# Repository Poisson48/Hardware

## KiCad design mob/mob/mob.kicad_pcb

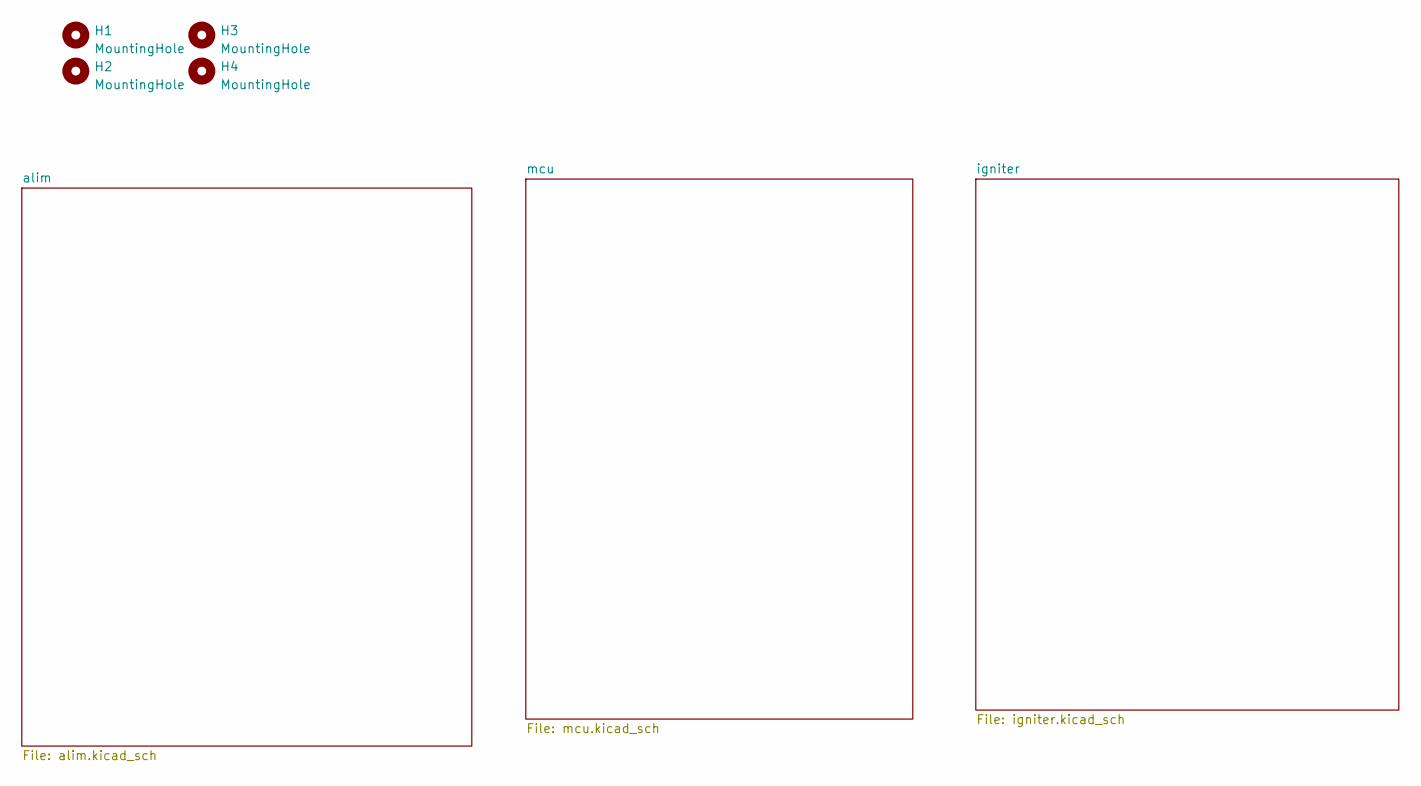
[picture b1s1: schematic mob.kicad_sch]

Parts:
H1, H2, H3, H4: MountingHole; MountingHole_3.2mm_M3_DIN965_Pad

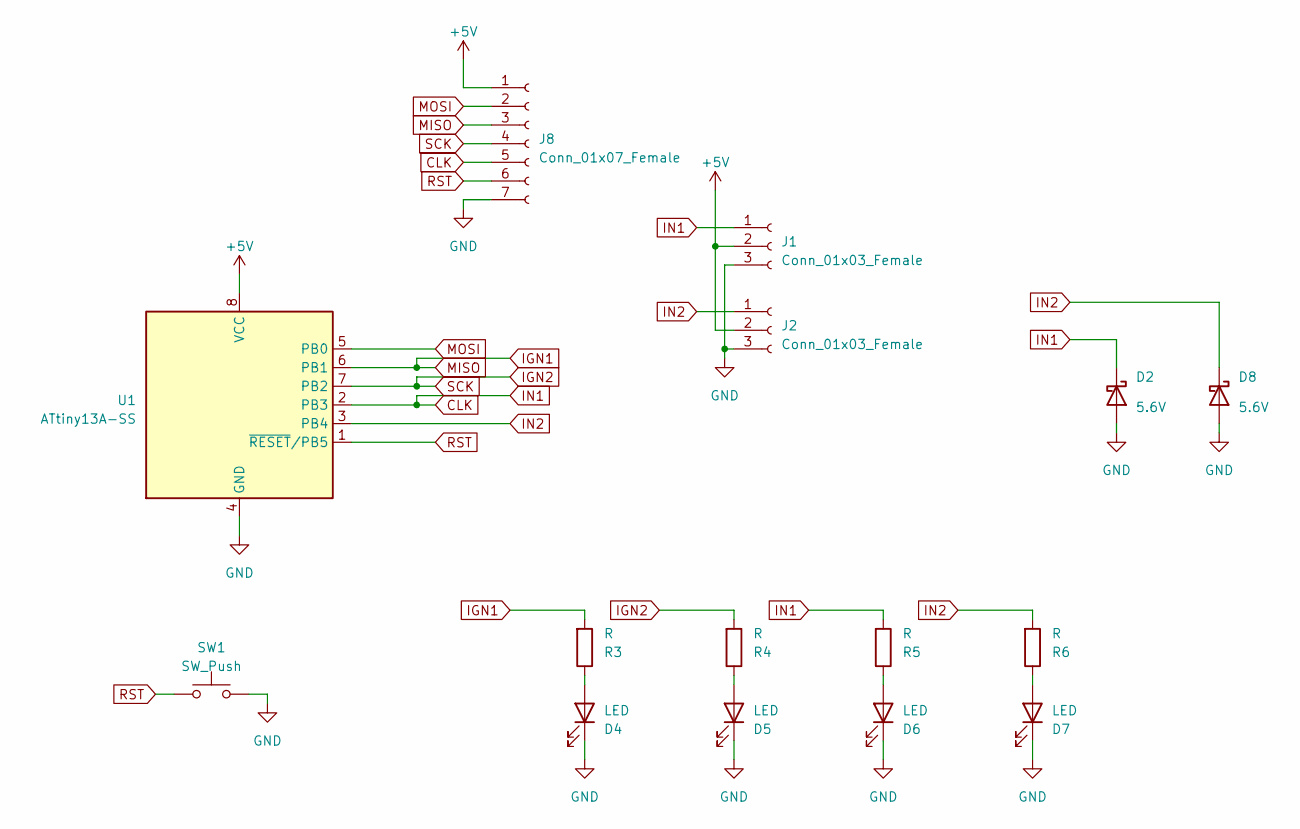
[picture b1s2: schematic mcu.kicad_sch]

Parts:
D2, D8: 5.6V; D_SOD-123
D4, D5, D6, D7: LED; D_0805_2012Metric
J1, J2: Conn_01x03_Female; PinSocket_1x03_P2.54mm_Vertical
J8: Conn_01x07_Female; PinSocket_1x07_P2.54mm_Vertical
R3, R4, R5, R6: R; R_0805_2012Metric
SW1: SW_Push; SW_PUSH_6mm
U1: ATtiny13A-SS; SOIC-8_3.9x4.9mm_P1.27mm

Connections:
+5V: J1.2, J2.2, J8.1, U1.8 (VCC); also elsewhere on the board
CLK: D2.1 (K), J1.1, J8.5, R5.2, U1.2 (PB3)
GND: D2.2 (A), D4.1 (K), D5.1 (K), D6.1 (K), D7.1 (K), D8.2 (A), J1.3, J2.3, J8.7, SW1.2, U1.4 (GND); also elsewhere on the board
IGN1: J8.3, R3.2, U1.6 (PB1); also elsewhere on the board
IGN2: J8.4, R4.2, U1.7 (PB2); also elsewhere on the board
IN2: D8.1 (K), J2.1, R6.2, U1.3 (PB4)
MOSI: J8.2, U1.5 (PB0)
unnamed: D4.2 (A), R3.1
unnamed: D5.2 (A), R4.1
unnamed: D6.2 (A), R5.1
unnamed: D7.2 (A), R6.1
RST: J8.6, SW1.1, U1.1 (~RESET/PB5)

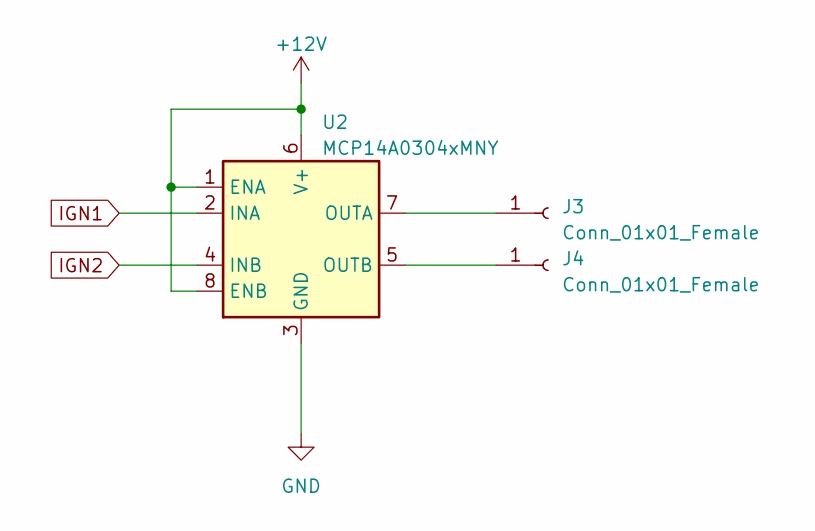
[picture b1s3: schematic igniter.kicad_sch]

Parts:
J3, J4: Conn_01x01_Female; Pin_D1.3mm_L11.0mm_LooseFit
U2: MCP14A0304xMNY; WDFN-8-1EP_3x2mm_P0.5mm_EP1.3x1.4mm

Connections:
+12V: U2.1 (ENA), U2.6 (V+), U2.8 (ENB); also elsewhere on the board
GND: U2.3 (GND), U2.9 (GND); also elsewhere on the board
IGN1: U2.2 (INA); also elsewhere on the board
IGN2: U2.4 (INB); also elsewhere on the board
unnamed: J3.1, U2.7 (OUTA)
unnamed: J4.1, U2.5 (OUTB)

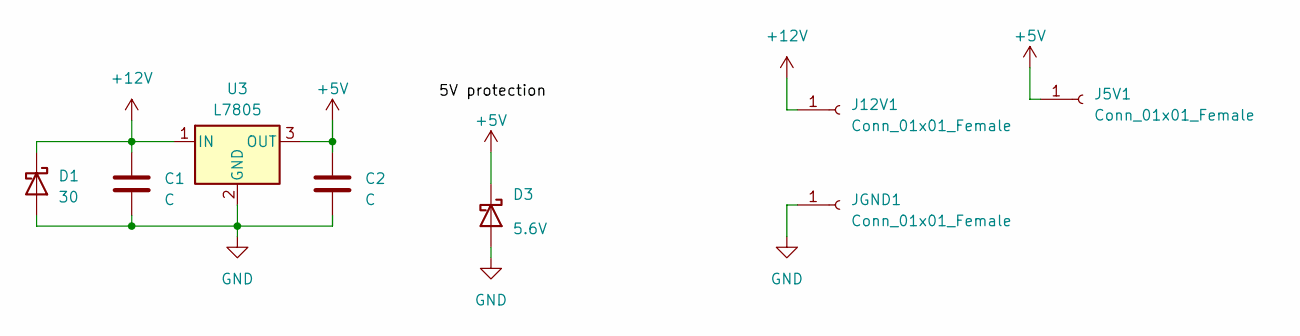
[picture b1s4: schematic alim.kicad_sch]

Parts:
C1, C2: C; C_1206_3216Metric
D1: 30; D_SOD-123
D3: 5.6V; D_SOD-123
J5V1, J12V1: Conn_01x01_Female; Pin_D1.3mm_L11.0mm_LooseFit
JGND1: Conn_01x01_Female; Pin_D1.3mm_L11.0mm_LooseFit
U3: L7805; TO-252-2

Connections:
+5V: C2.2, D3.1 (K), J5V1.1, U3.3 (OUT); also elsewhere on the board
+12V: C1.2, D1.1 (K), J12V1.1, U3.1 (IN); also elsewhere on the board
GND: C1.1, C2.1, D1.2 (A), D3.2 (A), JGND1.1, U3.2 (GND); also elsewhere on the board

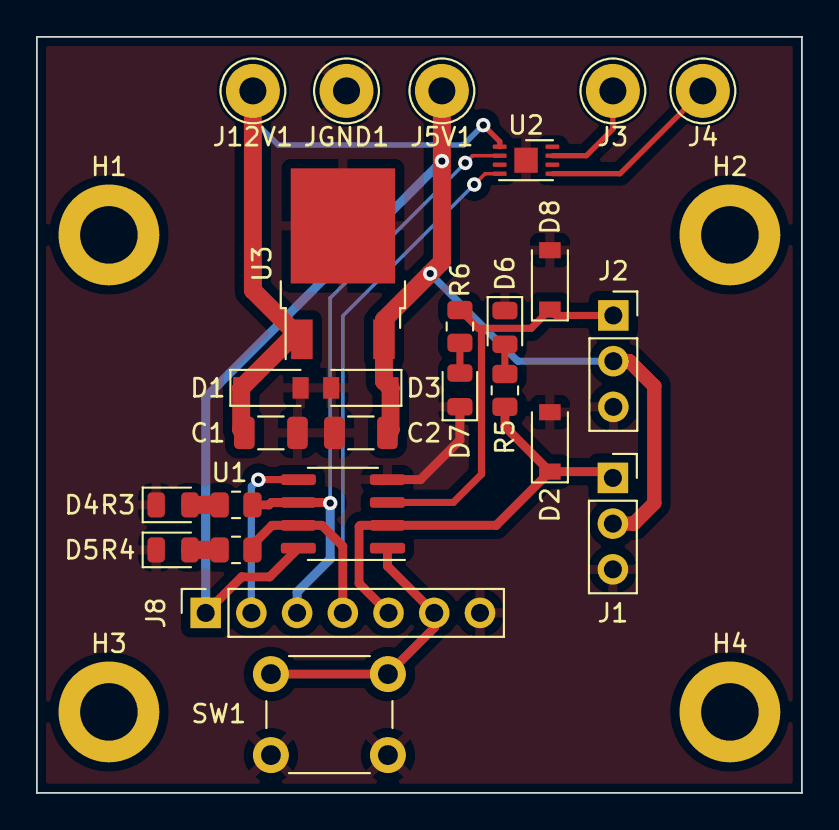
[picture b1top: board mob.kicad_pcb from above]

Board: 2 copper layers, 42.5 x 42.0 mm, 30 parts (0 on the bottom side), 15 nets.

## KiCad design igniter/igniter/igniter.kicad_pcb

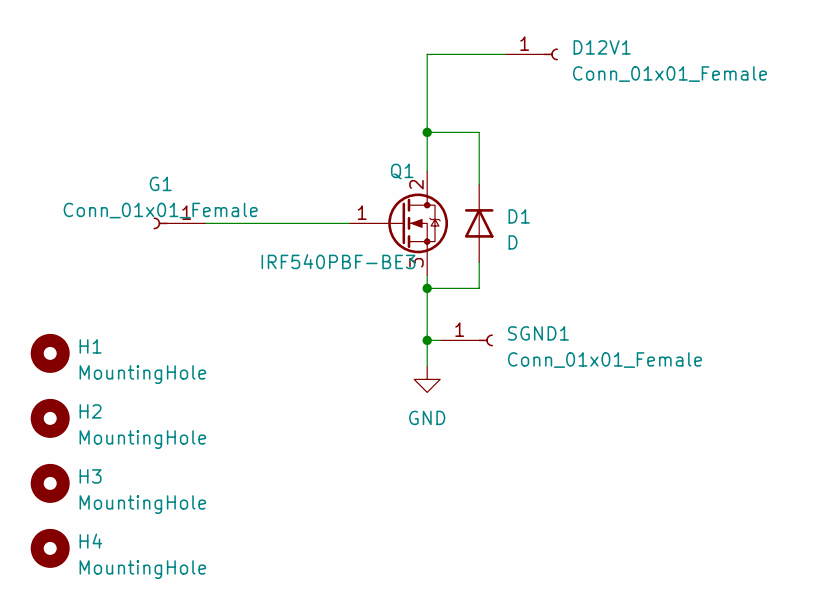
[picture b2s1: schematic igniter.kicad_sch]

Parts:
D1: D; TO-220-2_Horizontal_TabDown
D12V1: Conn_01x01_Female; Pin_D1.3mm_L11.0mm_LooseFit
G1: Conn_01x01_Female; Pin_D1.3mm_L11.0mm_LooseFit
H1, H2, H3, H4: MountingHole; MountingHole_3.2mm_M3_DIN965_Pad
Q1: IRF540PBF-BE3; TO-220-3_Horizontal_TabDown
SGND1: Conn_01x01_Female; Pin_D1.3mm_L11.0mm_LooseFit

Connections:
GND: D1.2 (A), Q1.3 (S), SGND1.1
unnamed: D1.1 (K), D12V1.1, Q1.2 (D)
unnamed: G1.1, Q1.1 (G)

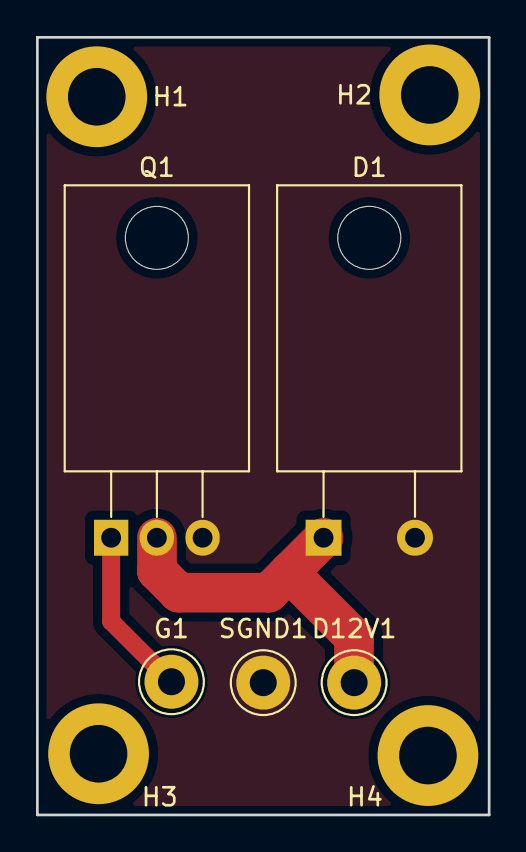
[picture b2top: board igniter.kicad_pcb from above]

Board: 2 copper layers, 25.1 x 43.2 mm, 9 parts (0 on the bottom side), 3 nets.

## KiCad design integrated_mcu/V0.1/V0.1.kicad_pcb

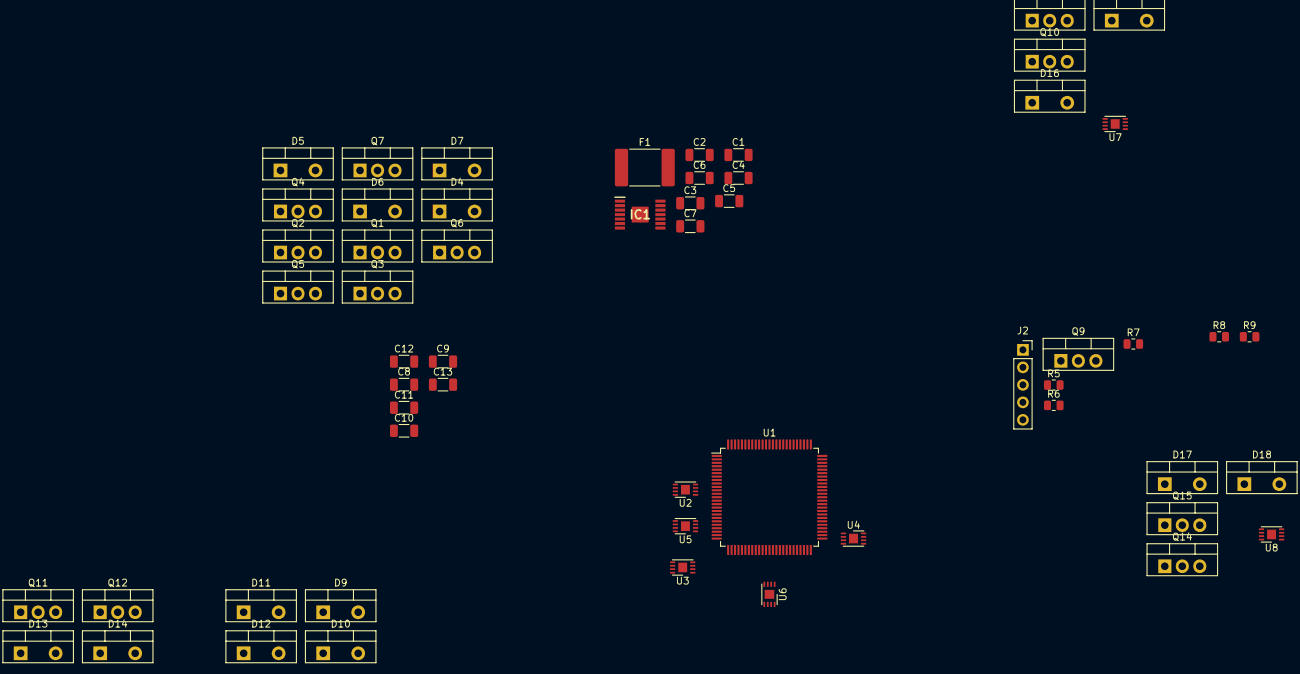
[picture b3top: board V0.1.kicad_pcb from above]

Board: 2 copper layers, 57 parts (0 on the bottom side), 59 nets, no tracks yet.

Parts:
C1, C4, C6, C7, C9, C10, C11, C12, C13: C; C_1206_3216Metric
C2, C3: 1μF; C_1206_3216Metric
C5: 10μF; C_1206_3216Metric
C8: 100nF; C_1206_3216Metric
D4, D5, D6, D7, D9, D10, D11, D12, D13, D14, D15, D16, D17, D18: D; TO-220-2_Vertical
F1: 576-2920L700/24SLER; Fuse_2920_7451Metric
IC1: TPS54225TPWPRQ1; SOP65P640X120-15N
J2: Conn_01x05_Female; PinSocket_1x05_P2.54mm_Vertical
Q1, Q2, Q3, Q4, Q5, Q6, Q7, Q9, Q10, Q11, Q12, Q13, Q14, Q15: IRF540PBF-BE3; TO-220-3_Vertical
R5: 10k; R_0805_2012Metric
R6: 2k; R_0805_2012Metric
R7, R8, R9: 1k; R_0805_2012Metric
U1: ATmega2560-16A; TQFP-100_14x14mm_P0.5mm
U2, U3, U4, U5, U6, U7, U8: MCP14A0304xMNY; WDFN-8-1EP_3x2mm_P0.5mm_EP1.3x1.4mm

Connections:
+5P: C7.2, IC1.1 (VO)
+5V: C10.1, C11.1, J2.2, R8.2, R9.2, U1.10 (VCC), U1.31 (VCC), U1.61 (VCC), U1.80 (VCC), U1.100 (AVCC)
+12P: C1.1, F1.1
+12V: C4.1, C5.2, F1.2, IC1.13 (VIN), IC1.14 (VCC), R5.2, U2.1 (ENA), U2.6 (V+), U2.8 (ENB), U3.1 (ENA), U3.6 (V+), U3.8 (ENB), U4.1 (ENA), U4.6 (V+), U4.8 (ENB), U5.1 (ENA), U5.6 (V+), U5.8 (ENB), U6.1 (ENA), U6.6 (V+), U6.8 (ENB), U7.1 (ENA), U7.6 (V+), U7.8 (ENB), U8.1 (ENA), U8.6 (V+), U8.8 (ENB)
BOOST: U1.16 (PH4), U8.2 (INA)
BOOST-OUT: D17.1 (K), Q14.2 (D)
FAN-CTRL: U1.37 (PL2), U6.4 (INB)
FAN-OUT: D14.1 (K), Q12.2 (D)
FUELPUMP-CTRL: U1.39 (PL4), U6.2 (INA)
FUELPUMP-OUT: D13.1 (K), Q11.2 (D)
GND: C1.2, C2.1, C3.1, C4.2, C5.1, C7.1, C8.2, C9.2, C10.2, C11.2, D4.2 (A), D5.2 (A), D6.2 (A), D7.2 (A), D9.2 (A), D10.2 (A), D11.2 (A), D12.2 (A), D13.2 (A), D14.2 (A), D15.2 (A), D16.2 (A), D17.2 (A), D18.2 (A), IC1.5 (GND), IC1.8 (PGND1), IC1.9 (PGND2), IC1.15 (EP), J2.3, Q1.3 (S), Q2.3 (S), Q3.3 (S), Q4.3 (S), Q5.3 (S), Q6.3 (S), Q7.3 (S), Q9.3 (S), Q10.3 (S), Q11.3 (S), Q12.3 (S), Q13.3 (S), Q14.3 (S), Q15.3 (S), R6.2, U2.3 (GND), U2.9 (GND), U3.3 (GND), U3.9 (GND), U4.3 (GND), U4.9 (GND), U5.3 (GND), U5.9 (GND), U6.3 (GND), U6.9 (GND), U7.3 (GND), U7.9 (GND), U8.3 (GND), U8.9 (GND)
IDLE: U1.15 (PH3), U8.4 (INB)
IDLE-OUT: D18.1 (K), Q15.2 (D)
IGN1: U1.52 (PG1), U4.2 (INA)
IGN2: U1.50 (PD7), U4.4 (INB)
IGN3: U1.20 (PB1), U5.4 (INB)
IGN4: U1.22 (PB3), U5.2 (INA)
IGNOUT1: D11.1 (K), Q5.2 (D)
IGNOUT2: D6.1 (K), Q7.2 (D)
IGNOUT4: D12.1 (K), Q6.2 (D)
INJ1: U1.17 (PH5), U2.4 (INB)
INJ2: U1.18 (PH6), U2.2 (INA)
INJ3: U1.23 (PB4), U3.4 (INB)
INJ4: U1.24 (PB5), U3.2 (INA)
INJOUT1: D4.1 (K), Q3.2 (D)
INJOUT2: D9.1 (K), Q1.2 (D)
INJOUT3: D5.1 (K), Q4.2 (D)
INJOUT4: D10.1 (K), Q2.2 (D)
MCU-BL: J2.1, U1.7 (PE5)
unnamed: C3.2, IC1.4 (SS)
unnamed: C6.2, IC1.10 (SW1), IC1.11 (SW2)
unnamed: C6.1, IC1.12 (VBST)
unnamed: C2.2, IC1.3 (VREG5)
unnamed: J2.5, R6.1, R7.2
unnamed: Q1.1 (G), U2.7 (OUTA)
unnamed: Q3.1 (G), U2.5 (OUTB)
unnamed: Q4.1 (G), U3.5 (OUTB)
unnamed: Q7.1 (G), U4.5 (OUTB)
unnamed: Q10.1 (G), U7.7 (OUTA)
unnamed: Q11.1 (G), U6.7 (OUTA)
unnamed: Q12.1 (G), U6.5 (OUTB)
unnamed: Q13.1 (G), U7.5 (OUTB)
unnamed: Q14.1 (G), U8.7 (OUTA)
unnamed: Q15.1 (G), U8.5 (OUTB)
unnamed: C8.1, U1.98 (AREF)
unnamed: U1.11 (GND), U1.32 (GND), U1.62 (GND), U1.81 (GND), U1.99 (GND)
unnamed: C9.1, U1.30 (~RESET)
unnamed: Q2.1 (G), U3.7 (OUTA)
unnamed: Q5.1 (G), U4.7 (OUTA)
unnamed: Q6.1 (G), U5.7 (OUTA)
SCL: R9.1, U1.43 (PD0)
SDA: R8.1, U1.44 (PD1)
SPARE1: U1.5 (PE3), U7.2 (INA)
SPARE2: U1.1 (PG5), U7.4 (INB)
SPARE-OUT1: D15.1 (K), Q10.2 (D)
SPARE-OUT2: D16.1 (K), Q13.2 (D)
TACHO-CTRL: Q9.1 (G), U1.35 (PL0)
TACHO-OUT: Q9.2 (D), R5.1
XTAL2: C13.2, U1.33 (XTAL2)

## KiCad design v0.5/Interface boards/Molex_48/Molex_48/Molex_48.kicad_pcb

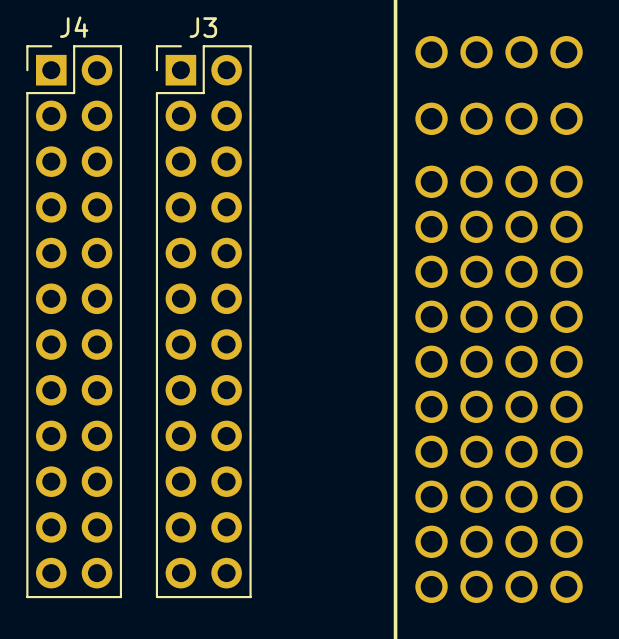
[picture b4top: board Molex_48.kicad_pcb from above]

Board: 2 copper layers, 3 parts (0 on the bottom side), 2 nets, no tracks yet.

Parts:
J2: 500762-0482; 5007620482
J3, J4: Conn_02x12_Counter_Clockwise; PinHeader_2x12_P2.54mm_Vertical

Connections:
+5V: J2.F3, J2.F4
GND: J2.H1, J2.H2, J2.H3, J2.H4, J2.J1, J2.J2, J2.J3, J2.J4, J2.L1, J2.L2, J2.L3, J2.L4, J2.M1, J2.M2, J2.M3, J2.M4, J3.1, J3.2, J3.3, J3.4, J3.7, J3.8, J3.9, J3.10, J4.1, J4.2, J4.3, J4.4, J4.7, J4.8, J4.9, J4.10

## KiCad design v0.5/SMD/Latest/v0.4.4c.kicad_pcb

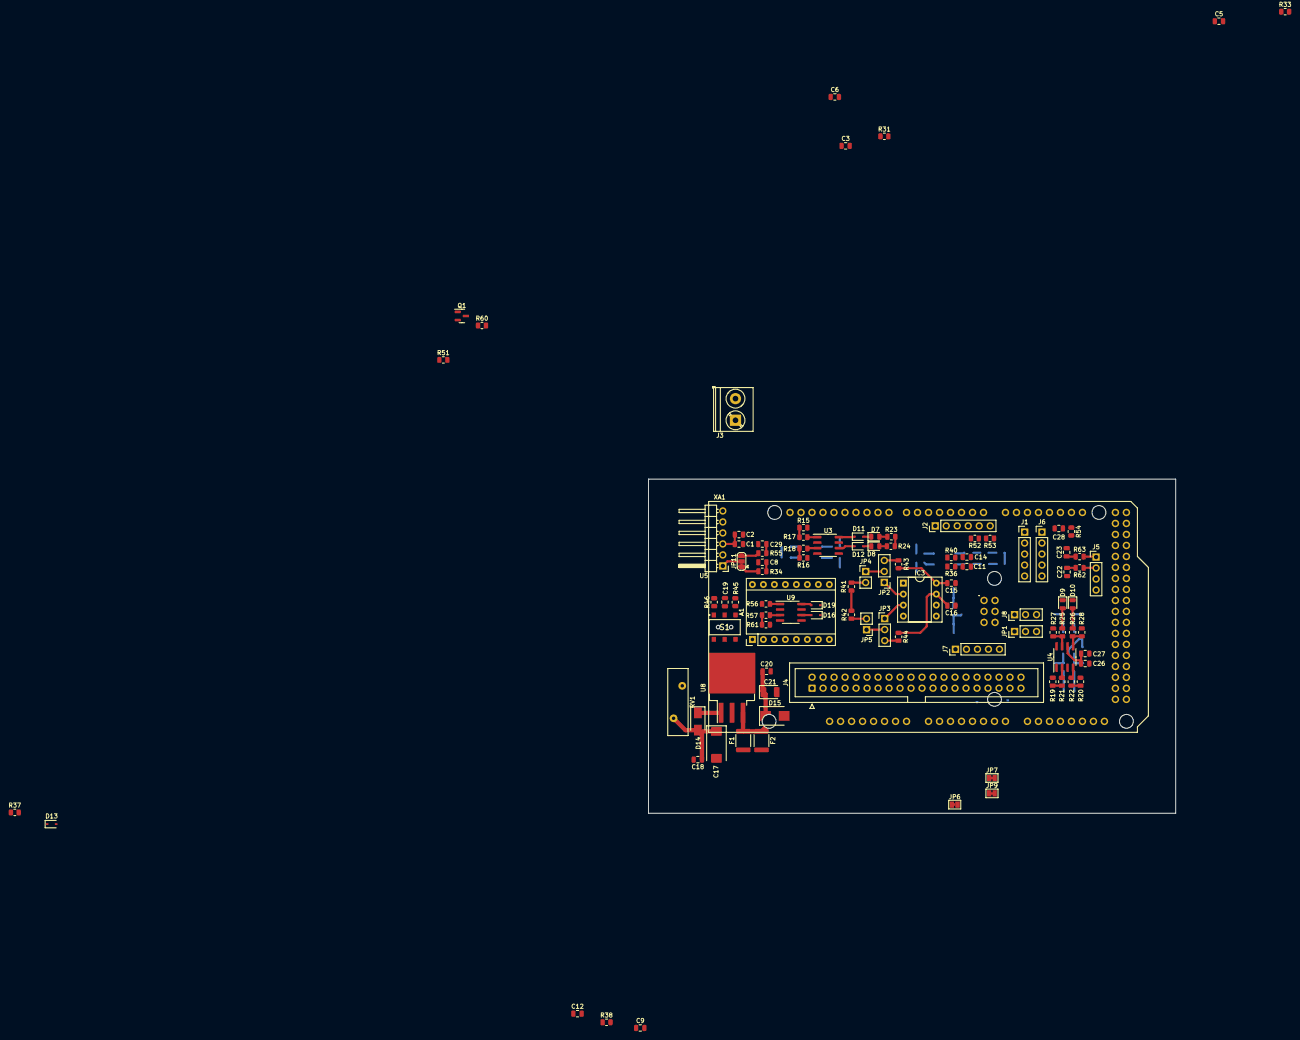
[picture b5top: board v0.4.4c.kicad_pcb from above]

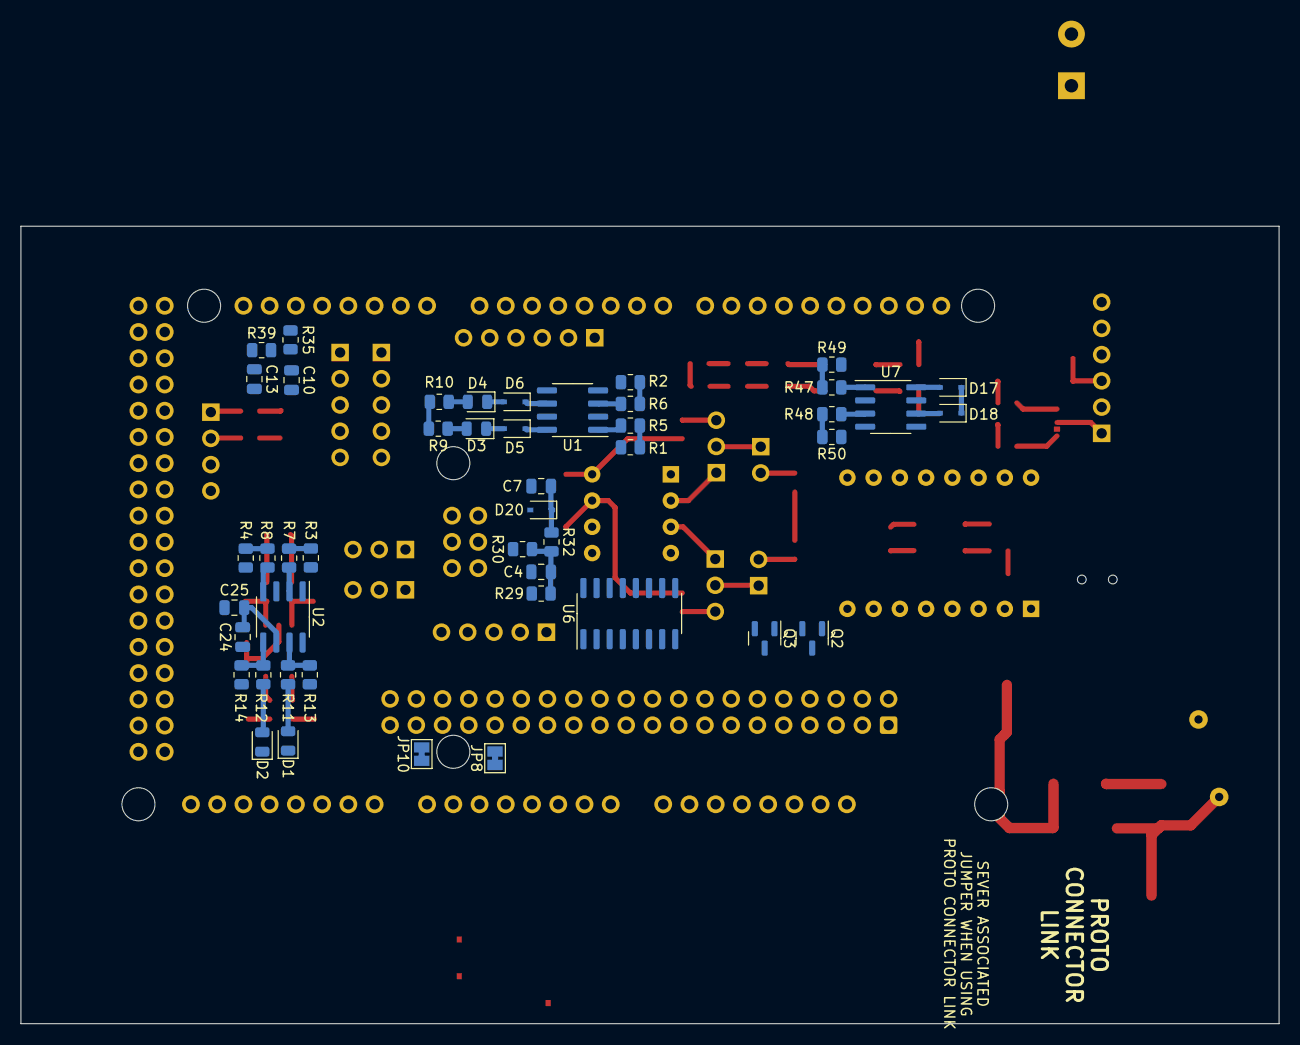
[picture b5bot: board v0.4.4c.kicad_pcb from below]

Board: 2 copper layers, 121.8 x 77.2 mm, 148 parts (46 on the bottom side), 120 nets.

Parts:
A1: Pololu_Breakout_DRV8825; Pololu_Breakout-16_15.2x20.3mm
C1, C15: 0.01uF; C_0805_2012Metric
C2, C25, C27: 1uF; C_0805_2012Metric
C3, C4, C9, C10, C11, C16, C18, C20, C22, C23, C24, C26, C28: 0.1uF; C_0805_2012Metric
C5, C6, C7, C12, C13, C14: 0.22uF; C_0805_2012Metric
C8, C29: 470pf; C_0805_2012Metric
C17: 10uF; CP_EIA-7343-31_Kemet-D
C19: 22uF; C_0805_2012Metric
C21: 47uF; CP_EIA-3528-21_Kemet-B
D1, D2, D3, D4, D7, D8, D9, D10: LED; LED_0805_2012Metric
D5, D6, D11, D12, D16, D17, D18, D19: D; D_SOD-323
D13, D20: D_Zener; D_SOD-323
D14: B130-13-F; D_SMA
D15: 1SMB5919BT3G; D_SMB
F1, F2: Polyfuse; Fuse_1812_4532Metric
IC3: Trig Cond Socket; DIP-8_W7.62mm_Socket
J1, J6, J7: Conn_01x05; PinHeader_1x05_P2.54mm_Vertical
J2: Conn_01x06; PinHeader_1x06_P2.54mm_Vertical
J3: Conn_01x02; TerminalBlock_Phoenix_PT-1,5-2-5.0-H_1x02_P5.00mm_Horizontal
J4: Conn_02x20_Counter_Clockwise; IDC-Header_2x20_P2.54mm_Vertical
J5: Conn_01x04; PinHeader_1x04_P2.54mm_Vertical
J8: Conn_01x03; PinHeader_1x03_P2.54mm_Vertical
JP1: Ignition Voltage; PinHeader_1x03_P2.54mm_Vertical
JP2, JP3: VR-HALL; PinHeader_1x03_P2.54mm_Vertical
JP4, JP5: PULL-UP; PinHeader_1x02_P2.54mm_Vertical
JP6, JP7, JP8, JP9, JP10: SolderJumper_2_Bridged; SolderJumper-2_P1.3mm_Bridged_Pad1.0x1.5mm
JP11: Jumper_3_Bridged12; SolderJumper-3_P1.3mm_Bridged12_RoundedPad1.0x1.5mm
Q1, Q2, Q3: SSM3K357R; SOT-23
R1, R2, R3, R4, R15, R16, R19, R20, R49, R50, R60, R61: 100k; R_0805_2012Metric
R5, R6, R7, R8, R17, R18, R21, R22, R29, R37, R41, R42, R47, R48, R53, R54, R56, R57: 1k; R_0805_2012Metric
R9, R10, R11, R12, R23, R24, R25, R26, R33: 2.4k; R_0805_2012Metric
R13, R14, R27, R28: 10R; R_0805_2012Metric
R30: 3.9k; R_0805_2012Metric
R31, R32, R34, R38, R39, R40, R55, R62, R63: 470R; R_0805_2012Metric
R35, R36: 2.49k; R_0805_2012Metric
R43, R44: 220R; R_0805_2012Metric
R45, R51: 10k; R_0805_2012Metric
R46: 120R; R_0805_2012Metric
R52: 2k; R_0805_2012Metric
RV1: Varistor; RV_Disc_D15.5mm_W4.7mm_P7.5mm
S1: AYZ0202AGRLC
U1, U3, U7, U9: VNLD5090; SOIC-8_3.9x4.9mm_P1.27mm
U2, U4: TC4424A; SOIC-8_3.9x4.9mm_P1.27mm
U5: MPX4250; PinHeader_1x06_P2.54mm_Horizontal
U6: SP720; SOIC-16_3.9x9.9mm_P1.27mm
U8: LM2940S-5.0/NOPB; TO-263-3_TabPin2
XA1: Arduino_Mega2560_Shield

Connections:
12V-SW: A1.8 (VMOT), C17.1, C18.1, D14.2 (A), D16.1 (K), D17.1 (K), D18.1 (K), D19.1 (K), J3.2, J8.1, J8.2, J8.3, JP1.3 (B), R9.2, R10.2, R23.2, R24.2, R30.2, R51.2, RV1.1
ADC-Clamp-1: C7.1, D20.1 (K), R32.1, U6.1 (I1), XA1.A4
ADC-Clamp-2: C8.2, R34.1, U6.2 (I2), XA1.A3
ADC-Clamp-3: C14.1, R40.1, U6.3 (I3), XA1.A1
ADC-Clamp-4: C12.1, R38.1, U6.4 (I4), XA1.A2
ADC-Clamp-5: C13.1, R39.1, U6.5 (I5), XA1.A0
ADC-Clamp-6: C6.1, R31.1, U6.6 (I6), XA1.A8
ADC-Clamp-8: C16.2, IC3.7, R44.1, U6.9 (I8), XA1.D18 (D18_TX1)
ADC-Clamp-9: C15.2, IC3.8, R43.1, U6.10 (I9), XA1.D19 (D19_RX1)
ADC-Clamp-10: C5.1, JP6.1 (A), R33.2, U6.11 (I10), XA1.D2 (D2_INT0)
ADC-Clamp-13: D13.1 (K), R37.2, U6.14 (I13), XA1.D51
BOOST-OUT: D17.2 (A), J4.12, U7.8 (DRAIN1)
CAM-IN: J4.34, JP3.2 (C), JP5.1 (A)
CLT_Sensor: C11.1, J4.37, R36.1, R40.2
CRANK-IN: J4.32, JP2.2 (C), JP4.1 (A)
Clutch_in: JP10.1 (A), R37.1
FAN-OUT: JP7.1 (A), Q2.3 (D)
FUELPUMP-OUT: JP8.1 (A), Q3.3 (D)
GND: A1.1 (GND), A1.7 (GND), C1.1, C2.1, C3.2, C4.2, C5.2, C6.2, C7.2, C8.1, C9.2, C10.2, C11.2, C12.2, C13.2, C14.2, C15.1, C16.1, C17.2, C18.2, C19.2, C20.2, C21.2, C22.2, C23.2, C24.1, C25.1, C26.1, C27.1, C28.1, C29.2, D1.1 (K), D2.1 (K), D9.1 (K), D10.1 (K), D13.2 (A), D15.2 (A), D20.2 (A), IC3.6, J2.3, J3.1, J4.17, J4.19, J4.23, J4.36, J6.1, J6.2, J6.3, J6.4, J6.5, Q1.2 (S), Q2.2 (S), Q3.2 (S), R1.2, R2.1, R3.2, R4.1, R15.2, R16.1, R19.2, R20.1, R29.1, R49.2, R50.1, R52.2, R60.2, R61.1, RV1.2, U1.5 (SOURCE2), U1.7 (SOURCE1), U2.3 (GND), U3.5 (SOURCE2), U3.7 (SOURCE1), U4.3 (GND), U5.2 (GND), U6.8 (GND), U7.5 (SOURCE2), U7.7 (SOURCE1), U8.2 (GND), U9.5 (SOURCE2), U9.7 (SOURCE1), XA1.GND1 (GND), XA1.GND2 (GND), XA1.GND3 (GND), XA1.GND5 (GND), XA1.GND6 (GND)
HC-1-OUT: D18.2 (A), J4.10, U7.6 (DRAIN2)
HC-2-OUT: D16.2 (A), J4.6, U9.6 (DRAIN2)
IAT_Sensor: C10.1, J4.39, R35.1, R39.2
IDLE-OUT: D19.2 (A), J4.8, U9.8 (DRAIN1)
IGN-1-OUT: J4.13, R14.1
IGN-2-OUT: J4.14, R13.1
IGN-3-OUT: J4.16, R28.1
IGN-4-OUT: J4.15, R27.1
INJ-1-OUT: D5.1 (K), J4.1, J4.2, U1.8 (DRAIN1)
INJ-2-OUT: D11.1 (K), J4.3, J4.4, U3.8 (DRAIN1)
INJ-3-OUT: D12.1 (K), J4.5, J4.7, U3.6 (DRAIN2)
INJ-4-OUT: D6.1 (K), J4.9, J4.11, U1.6 (DRAIN2)
MAP-EXT: J4.21, JP11.1 (A), R34.2
MCU-A5: C29.1, R55.1, XA1.A5
MCU-A9: C23.1, R63.1, XA1.A9
MCU-A10: C22.1, R62.2, XA1.A10
MCU-D0: J2.4, XA1.D0 (D0_RX0)
MCU-D1: R53.1, XA1.D1 (D1_TX0)
MCU-D3: J2.1, XA1.D3 (D3_INT1)
MCU-D4: R57.2, R61.2, XA1.D4
MCU-D5: R56.2, R60.1, XA1.D5
MCU-D6: R48.2, R50.2, XA1.D6
MCU-D7: R47.2, R49.1, XA1.D7
MCU-D8: R1.1, R5.2, XA1.D8
MCU-D9: R15.1, R17.2, XA1.D9
MCU-D10: R16.2, R18.2, XA1.D10
MCU-D11: R2.2, R6.2, XA1.D11
MCU-D16: A1.16 (DIR), XA1.D16 (D16_TX2)
MCU-D17: A1.15 (STEP), XA1.D17 (D17_RX2)
MCU-D20: C28.2, J5.4, R54.1, XA1.D20 (D20_SDA)
MCU-D21: J5.3, XA1.D21 (D21_SCL)
MCU-D24: A1.9 (~EN), XA1.D24
MCU-D38: R3.1, R7.2, XA1.D38
MCU-D40: R4.2, R8.2, XA1.D40
MCU-D45: Q3.1 (G), XA1.D45
MCU-D47: Q2.1 (G), XA1.D47
MCU-D49: Q1.1 (G), XA1.D49
MCU-D50: R19.1, R21.2, XA1.D50
MCU-D52: R20.2, R22.2, XA1.D52
unnamed: C4.1, R29.2, R30.1, R32.2
unnamed: C19.1, R46.1, S1.1 (NC_1)
unnamed: D1.2 (A), R11.2
unnamed: D2.2 (A), R12.2
unnamed: D3.1 (K), D5.2 (A)
unnamed: D3.2 (A), R9.1
unnamed: D4.1 (K), D6.2 (A)
unnamed: D4.2 (A), R10.1
unnamed: D7.2 (A), R23.1
unnamed: D8.2 (A), R24.1
unnamed: D9.2 (A), R25.2
unnamed: D10.2 (A), R26.2
unnamed: D7.1 (K), D11.2 (A)
unnamed: D8.1 (K), D12.2 (A)
unnamed: F2.2, J1.1, J1.2, J1.3, J1.4, J1.5
unnamed: IC3.2, JP2.1 (A)
unnamed: IC3.3, JP3.1 (A)
unnamed: J2.5, R52.1, R53.2
unnamed: J5.1, R63.2
unnamed: J5.2, R62.1
unnamed: JP2.3 (B), R43.2
unnamed: JP3.3 (B), R44.2
unnamed: JP4.2 (B), R41.1
unnamed: JP5.2 (B), R42.1
unnamed: JP11.2 (C), U5.1 (VOUT)
unnamed: JP11.3 (B), R55.2
unnamed: R5.1, U1.1 (IN1)
unnamed: R6.1, U1.3 (IN2)
unnamed: R7.1, U2.2 (IN_A)
unnamed: R8.1, U2.4 (IN_B)
unnamed: R11.1, R13.2, U2.7 (OUT_A)
unnamed: R12.1, R14.2, U2.5 (OUT_B)
unnamed: R17.1, U3.1 (IN1)
unnamed: R18.1, U3.3 (IN2)
unnamed: R21.1, U4.2 (IN_A)
unnamed: R22.1, U4.4 (IN_B)
unnamed: R25.1, R27.2, U4.7 (OUT_A)
unnamed: R26.1, R28.2, U4.5 (OUT_B)
unnamed: R45.1, S1.3 (NO_1)
unnamed: R47.1, U7.1 (IN1)
unnamed: R48.1, U7.3 (IN2)
unnamed: R56.1, U9.1 (IN1)
unnamed: R57.1, U9.3 (IN2)
O2_Sensor: C3.1, J4.40, R31.2
PROTO-1: J4.27, J7.1, JP6.2 (B)
PROTO-2: J4.29, J7.2, JP7.2 (B)
PROTO-3: J4.31, J7.3, JP8.2 (B)
PROTO-4: J4.33, J7.4, JP9.2 (B)
PROTO-5: J4.35, J7.5, JP10.2 (B)
RESET: S1.2 (C_1), XA1.RST1 (RESET)
STEP-A1: A1.4 (A1), J4.20
STEP-A2: A1.3 (A2), J4.18
STEP-B1: A1.5 (B1), J4.22
STEP-B2: A1.6 (B2), J4.24
TACHO-OUT: JP9.1 (A), Q1.3 (D), R51.1
TPS_Sensor: C9.1, J4.38, R38.2
VDD: A1.13 (~RST), A1.14 (~SLP), C1.2, C2.2, C20.1, C21.1, D15.1 (K), F1.2, F2.1, IC3.5, J2.2, JP1.1 (A), R45.2, R46.2, R54.2, U5.3 (VCC), U8.3 (VO), XA1.5V1 (5V), XA1.5V3 (5V), XA1.5V4 (5V)
VDDA: F1.1, J4.25, J4.26, R33.1, R35.2, R36.2, R41.2, R42.2, U6.16 (V+)
VR1-: IC3.1, J4.28
VR2-: IC3.4, J4.30
VRegIn: D14.1 (K), U8.1 (VI)
Vdrive: C24.2, C25.2, C26.2, C27.2, JP1.2 (C), U2.6 (VDD), U4.6 (VDD)

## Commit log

2021-12-07 new kicad format
2021-12-07 placing components
2022-01-04 adaptater
2022-01-23 updates!
